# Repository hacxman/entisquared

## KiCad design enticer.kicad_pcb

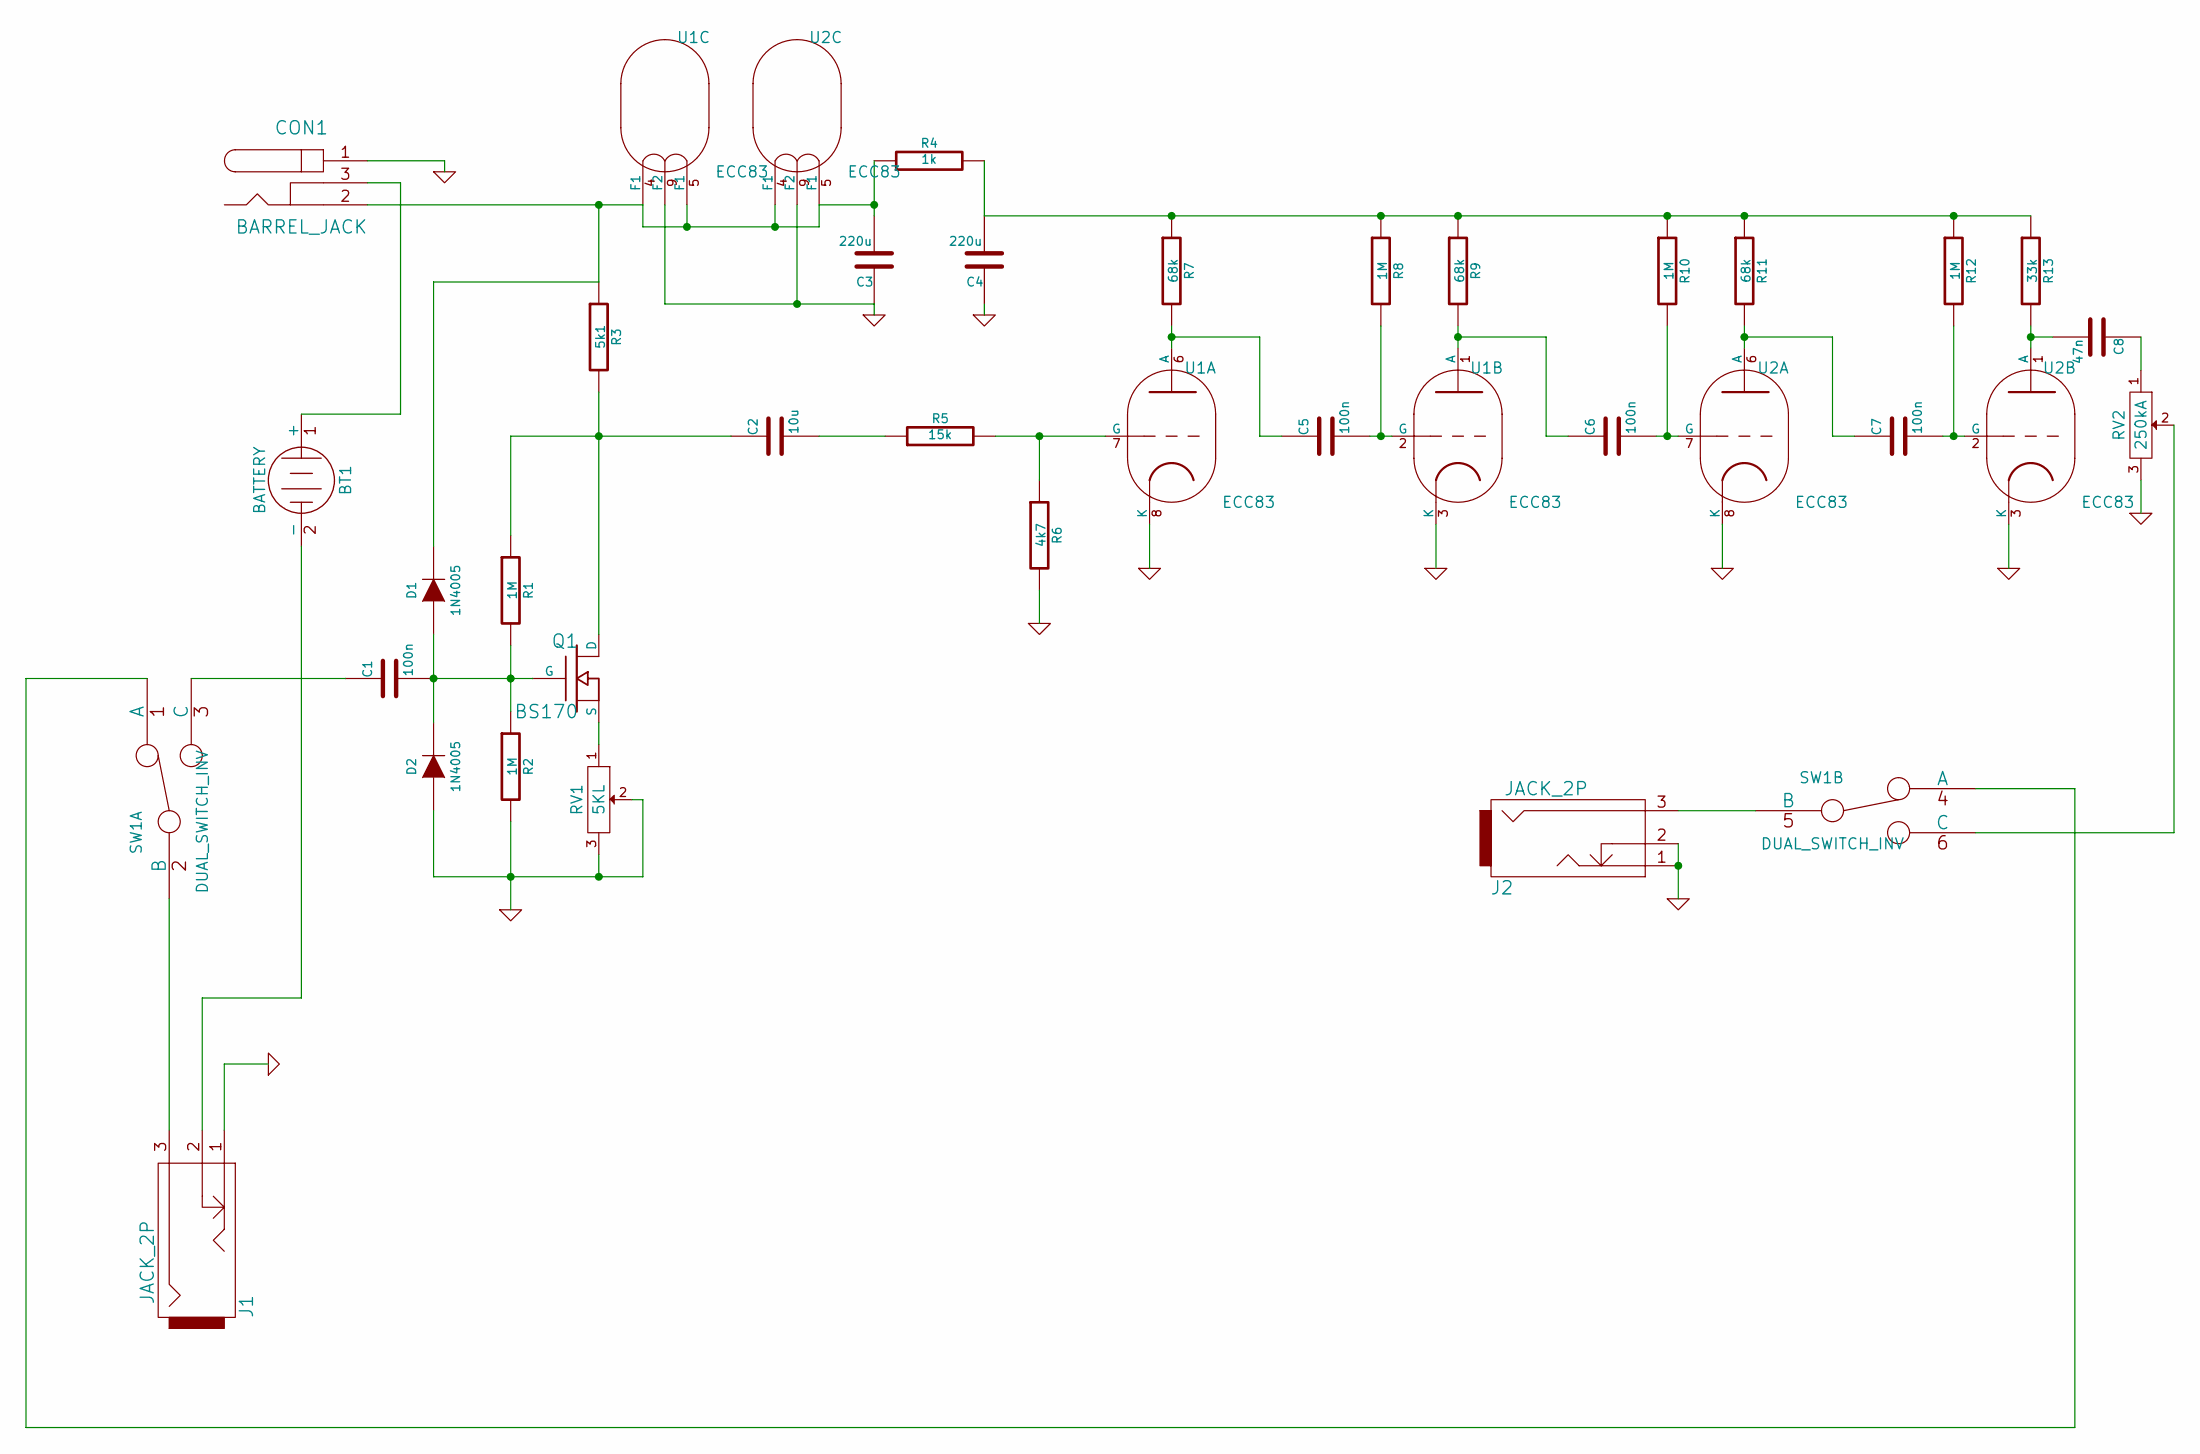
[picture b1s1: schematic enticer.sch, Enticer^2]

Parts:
BT1: BATTERY
C1, C5, C6, C7: 100n
C2: 10u
C3, C4: 220u
C8: 47n
CON1: BARREL_JACK
D1, D2: 1N4005
J1, J2: JACK_2P
Q1: BS170
R1, R2, R8, R10, R12: 1M
R3: 5k1
R4: 1k
R5: 15k
R6: 4k7
R7, R9, R11: 68k
R13: 33k
RV1: 5KL
RV2: 250kA
SW1: DUAL_SWITCH_INV
U1, U2: ECC83; VALVE-NOVAL_P

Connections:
GND: C3.1, C4.1, CON1.1, D2.1 (A), J1.1, J2.1, J2.2, R2.2, R6.2, RV1.2, RV1.3, RV2.3, U1.3 (K), U1.8 (K), U1.9 (F2), U2.3 (K), U2.8 (K), U2.9 (F2)
unnamed: C8.2, R13.2, U2.1 (A)
unnamed: C7.1, R11.2, U2.6 (A)
unnamed: C7.2, R12.2, U2.2 (G)
unnamed: C8.1, RV2.1
unnamed: C1.1, SW1.3 (C)
unnamed: SW1.1 (A), SW1.4 (A)
unnamed: J2.3, SW1.5 (B)
unnamed: RV2.2, SW1.6 (C)
unnamed: BT1.2 (-), J1.2
unnamed: J1.3, SW1.2 (B)
unnamed: BT1.1 (+), CON1.3
unnamed: C1.2, D1.1 (A), D2.2 (K), Q1.G, R1.2, R2.1
unnamed: C2.2, R5.1
unnamed: C2.1, Q1.D, R1.1, R3.2
unnamed: Q1.S, RV1.1
unnamed: C5.1, R7.2, U1.6 (A)
unnamed: C6.2, R10.2, U2.7 (G)
unnamed: C5.2, R8.2, U1.2 (G)
unnamed: C6.1, R9.2, U1.1 (A)
unnamed: R5.2, R6.1, U1.7 (G)
unnamed: C4.2, R4.2, R7.1, R8.1, R9.1, R10.1, R11.1, R12.1, R13.1

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
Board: 2 copper layers, 33 parts (0 on the bottom side), 24 nets, no tracks yet.

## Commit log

2015-05-22 initial
